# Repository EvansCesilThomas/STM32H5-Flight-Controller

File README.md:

# STM32H5 General Autopilot

A high-performance, compact autopilot utilizing the modern STM32H5 architecture.

<br>

## Features

* **Power Input:** 2S - 6S LiPo compatible
* **Dual BEC System:** 
    * `5V @ 2A` (Fixed)
    * `5V / 6V / 9V / 10V @ 2A` (Selectable)
* **Onboard Sensors:**
  * **IMU:** BMI270 or ICM-42688-P
  * **Barometer:** BMP280
  * **Compass:** QMC5883L
* **Connectivity:**
  * 6x UARTs
  * 1x I2C
  * MicroSD Card Slot
* **Signaling & Peripherals:**
  * WS2812B Addressable LED Strip Output
  * **7x Configurable GPIOs:**
    * 1x Analog Input
    * 2x Extra ESC Outputs (bringing total potential ESC outputs to 6)
    * 1x Timer Output
    * 3x Regular GPIOs
* Onboard monitoring of battery voltage and current, servo and 5V rail voltage.

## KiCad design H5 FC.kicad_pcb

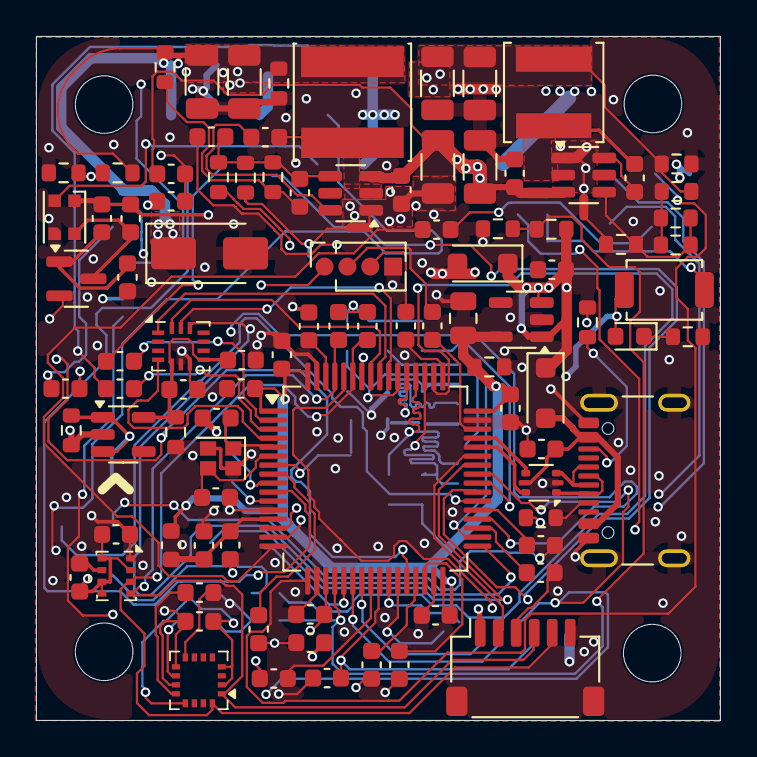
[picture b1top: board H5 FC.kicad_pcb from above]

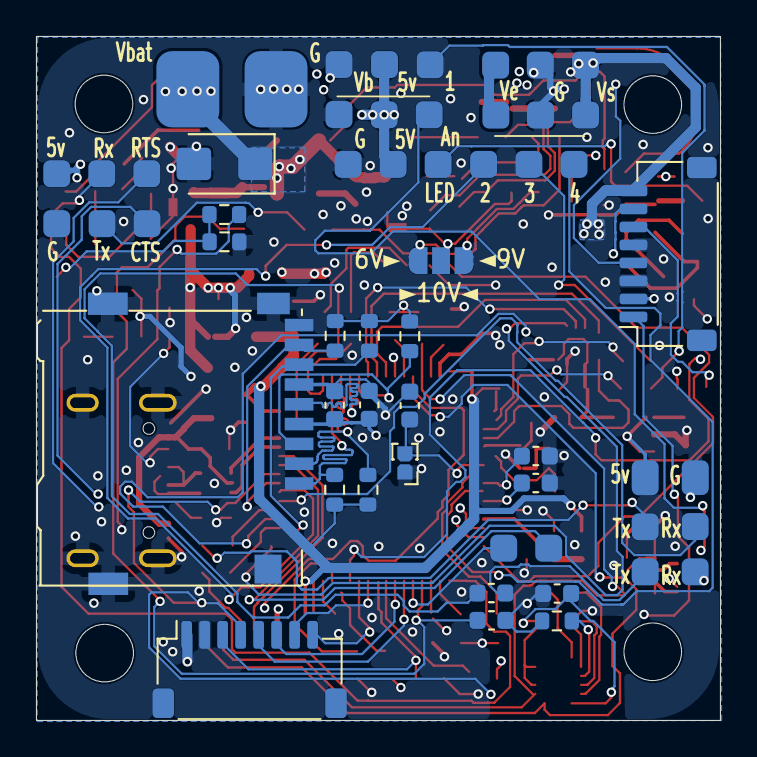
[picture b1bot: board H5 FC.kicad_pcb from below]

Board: 4 copper layers, 38.0 x 38.0 mm, 130 parts (25 on the bottom side), 99 nets.

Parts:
C1, C2: 2.2 uF; C_0603_1608Metric
C3, C9, C10, C11, C12, C13, C14, C15, C16, C17, C18, C19, C20, C21, C22, C23, C24, C26, C32, C33, C42, C43, C44, C46: 0.1uF; C_0603_1608Metric
C4, C28: 2.2uF; C_0603_1608Metric
C6, C7: 15pF; C_0603_1608Metric
C8: 4.7uF; C_0805_2012Metric
C25: 6.8uF; R_0603_1608Metric
C27: 75pF; R_0603_1608Metric
C29, C30: 2.2uF; R_0603_1608Metric
C31: 4.7uF; R_0603_1608Metric
C34, C35, C37, C38, C39, C40: 22uF; C_1206_3216Metric
C36: 75pF; C_0603_1608Metric
C41: 10uF; C_0603_1608Metric
C45: 0.22uF; C_0603_1608Metric
C47, C48: 0.1uF; R_0603_1608Metric
D1: LED; LED_0603_1608Metric
D2: SMAJ28A; D_SMA
D3: WS2812B; LED_WS2812B-2020_PLCC4_2.0x2.0mm
D4, D5: PMEG1030EH; D_SOD-123F
D7: SMAJ9.0A; D_SMA
H1, H2, H3, H4: MountingHole; MountingHole_3.2mm_M3
J1: Conn_01x04_Pin; PinSocket_1x04_P1.27mm_Vertical
J2: USB_C_Receptacle_USB2.0_16P; USB_C_Receptacle_GCT_USB4105-xx-A_16P_TopMnt_Horizontal
J3, J5: Conn_01x08; JST_SH_SM08B-SRSS-TB_1x08-1MP_P1.00mm_Horizontal
J4: Micro_SD_Card; microSD_HC_Hirose_DM3AT-SF-PEJM5
J6: Conn_01x03; JST_SH_SM04B-SRSS-TB_1x04-1MP_P1.00mm_Horizontal
J7: Conn_01x02; JST_SH_SM02B-SRSS-TB_1x02-1MP_P1.00mm_Horizontal
J8: Conn_01x05; JST_SH_BM08B-SRSS-TB_1x08-1MP_P1.00mm_Vertical
J9: Conn_01x06; JST_GH_SM05B-GHS-TB_1x05-1MP_P1.25mm_Horizontal
J13, J16, J17: Conn_01x06; JST_SH_SM06B-SRSS-TB_1x06-1MP_P1.00mm_Horizontal
J14: Conn_01x06; JST_SH_BM06B-SRSS-TB_1x06-1MP_P1.00mm_Vertical
JP2: Jumper_2_Bridged; PinHeader_1x02_P1.00mm_Vertical
JP3: SolderJumper_3_Bridged123; SolderJumper-3_P1.3mm_Bridged123_RoundedPad1.0x1.5mm_Number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
L1: 600 ohm; L_0603_1608Metric
L3: 15uH; L_Sunlord_SWPA5040S
L4: 22uH; L_Sunlord_SWPA6045S
NT1, NT2: NetTie_2; NetTie-2_SMD_Pad0.5mm
Q1: BC847; SOT-23
R1: 1.8K; R_0603_1608Metric
R2, R5, R6, R7, R8, R9, R11, R12, R24: 10K; R_0603_1608Metric
R3, R4: 5.1K; R_0603_1608Metric
R13, R18: 49.9; R_0603_1608Metric
R14: 105K; R_0603_1608Metric
R15, R20: 13.3K; R_0603_1608Metric
R17: 220; R_0603_1608Metric
R19, R23: 100K; R_0603_1608Metric
R21: 63.4K; R_0603_1608Metric
R22: 12K; C_0603_1608Metric
R25: 15K; C_0603_1608Metric
R31, R49, R50: 2.2K; C_0603_1608Metric
R32: 1K; C_0603_1608Metric
R34: 1.2K; C_0603_1608Metric
R38, R39, R40, R42, R45, R47, R48: 100; C_0603_1608Metric
R41, R46: 33; C_0603_1608Metric
R43, R44: 470; C_0603_1608Metric
R51: 4.7K; C_0603_1608Metric
R52: 10K; C_0603_1608Metric
SW1: SW_Push; SW_SPST_TS-1088-xR020
U1: STM32H562RITx; LQFP-64_10x10mm_P0.5mm
U2: BMI270; Bosch_LGA-14_3x2.5mm_P0.5mm
U3: BMP280; Bosch_LGA-8_2x2.5mm_P0.65mm_ClockwisePinNumbering
U5, U8: TPS54202DDC; SOT-23-6
U6: MIC5219-3.3YM5-MS; SOT-23-5
U7: MIC5205-3.3YM5-MS; SOT-23-5
U9: USBLC6-2P6; SOT-666
U11: QMC5883L; LGA-16_3x3mm_P0.5mm
Y2: 24 Mhz; Crystal_SMD_2016-4Pin_2.0x1.6mm

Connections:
5V_Sens: C21.1, R11.2, R12.1, U1.20 (PA4)
+3.3V: C8.1, C9.1, C10.1, C11.1, C13.1, C15.1, C18.1, C19.1, C29.1, C41.1, C42.1, C44.1, C46.1, D1.2 (A), J1.1, J4.4 (VDD), L1.1, R5.1, R6.1, R7.1, R8.1, R9.1, R49.2, R50.2, SW1.1, U1.1 (VBAT), U1.19 (VDD), U1.32 (VDD), U1.48 (VDD), U1.64 (VDD), U3.2 (CSB), U3.5 (SDO), U3.6 (VDDIO), U3.8 (VDD), U6.5 (OUT), U11.2 (VDD), U11.4 (S1), U11.13 (VDDIO)
+3.3V_IMU: C12.1, C14.1, C31.1, U2.5 (VDDIO), U2.8 (VDD), U7.5 (OUT)
+5V: C28.1, C30.1, D3.1 (VDD), D4.1 (K), D5.1 (K), J5.2, J6.3, J8.1, J13.1, J14.1, J16.1, J17.1, R11.1, R31.2, R51.2, U6.1 (IN), U6.3 (EN), U7.1 (IN), U7.3 (EN)
Analog_IN1: C22.1, J6.2, R32.1
BOOT0: R1.2, U1.60 (BOOT0)
GND: C1.2, C2.2, C3.2, C4.2, C6.2, C7.2, C8.2, C9.2, C10.2, C11.2, C12.2, C13.2, C14.2, C15.2, C16.2, C17.2, C18.2, C19.2, C20.2, C21.2, C22.2, C23.2, C25.2, C26.2, C28.2, C29.2, C30.2, C31.2, C32.2, C34.2, C35.2, C37.2, C38.2, C39.2, C40.2, C41.2, C42.2, C43.2, C44.2, C46.2, C47.2, C48.2, D2.2 (A2), D3.3 (VSS), D7.2 (A2), J1.4, J2.A1 (GND), J2.A12 (GND), J2.B1 (GND), J2.B12 (GND), J2.S1 (SHIELD), J3.2, J4.6 (VSS), J4.11 (SHIELD), J5.3, J5.5, J8.3, J8.5, J9.3, J9.4, J13.6, J14.4, J16.6, J17.6, JP2.1 (A), NT1.1, NT2.1, R2.1, R3.2, R4.2, R12.2, R17.2, R24.2, R34.2, R52.1, U1.12 (VSSA), U1.18 (VSS), U1.31 (VSS), U1.47 (VSS), U1.63 (VSS), U2.6 (GNDIO), U2.7 (GND), U3.1 (GND), U3.7 (GND), U5.1 (GND), U6.2 (GND), U7.2 (GND), U8.1 (GND), U9.2 (GND), U11.9 (GND), U11.11 (GND), Y2.2, Y2.4
GPIO1: J6.1, R44.1
GPIO2: J14.6, U1.39 (PC8)
GPIO3: J14.3, R43.1
GPIO4~_ADC: J14.5, U1.10 (PC2)
GPIO5~_ADC: J7.2, U1.21 (PA5)
GPIO6~: J7.1, U1.42 (PA9)
I2C1_SCL: J17.4, R49.1, U1.61 (PB8), U3.4 (SCK), U11.1 (SCL)
I2C1_SDA: J17.5, R50.1, U1.59 (PB7), U3.3 (SDI), U11.16 (SDA)
IBatt_Sens: C17.1, J3.3, U1.25 (PC5)
IMU_INT: U1.4 (PC15), U2.4 (INT1)
LED_OUT: Q1.2 (E), U1.28 (PB2)
LED_Strip: D3.2 (DOUT), J14.2
MOT1_PWM: J3.5, U1.22 (PA6)
MOT2_PWM: J3.6, U1.23 (PA7)
MOT3_PWM: J3.7, U1.26 (PB0)
MOT4_PWM: J3.8, U1.27 (PB1)
NRST: C26.1, JP2.2 (B), U1.7 (NRST)
unnamed: C1.1, U1.62 (VCAP)
unnamed: C2.1, U1.30 (VCAP)
unnamed: C27.1, R13.2, R14.1
unnamed: C36.1, R18.2, R19.1
unnamed: D1.1 (K), R17.1
unnamed: D3.4 (DIN), Q1.3 (C), R31.1
unnamed: J2.A5 (CC1), R4.1
unnamed: J2.B5 (CC2), R3.1
unnamed: JP3.1 (A), R25.2
unnamed: JP3.3 (B), R21.2
unnamed: JP3.2 (C), NT1.2, R20.2
unnamed: NT2.2, R15.2
unnamed: Q1.1 (B), R51.1, R52.2
unnamed: R1.1, R2.2, SW1.2
unnamed: R42.2, U1.16 (PA2)
unnamed: R47.2, U1.46 (PA13(JTMS)
unnamed: R48.2, U1.49 (PA14(JTCK)
unnamed: R46.1, U1.50 (PA15(JTDI))
unnamed: R38.1, U1.58 (PB6)
unnamed: R45.1, U1.29 (PB10)
unnamed: R40.1, U1.35 (PB14)
unnamed: R32.2, U1.8 (PC0)
unnamed: R39.2, U1.24 (PC4)
unnamed: R41.2, U1.37 (PC6)
unnamed: R43.2, U1.2 (PC13)
unnamed: R44.2, U1.3 (PC14)
unnamed: C6.1, U1.5 (PH0), Y2.1
unnamed: C7.1, U1.6 (PH1), Y2.3
unnamed: C3.1, C4.1, L1.2, U1.13 (VDDA)
unnamed: C24.1, U5.6 (BOOT)
unnamed: C27.2, R14.2, R15.1, U5.4 (FB)
unnamed: C24.2, L3.1, U5.2 (SW)
unnamed: C33.1, U8.6 (BOOT)
unnamed: C36.2, R19.2, R20.1, R21.1, R25.1, U8.4 (FB)
unnamed: C33.2, L4.1, U8.2 (SW)
unnamed: C25.1, U11.10 (C1)
unnamed: C45.1, U11.12 (SETC)
unnamed: C45.2, U11.8 (SETP)
SDMMC_CK: J4.5 (CLK), U1.53 (PC12)
SDMMC_CMD: J4.3 (CMD), R9.2, U1.54 (PD2)
SDMMC_D0: J4.7 (DAT0), R8.2, U1.34 (PB13)
SDMMC_D1: J4.8 (DAT1), R5.2, U1.40 (PC9)
SDMMC_D2: J4.1 (DAT2), R6.2, U1.51 (PC10)
SDMMC_D3: J4.2 (DAT3/CD), R7.2, U1.52 (PC11)
SPI1_CS1: U1.33 (PB12), U2.12 (CSB)
SPI1_MISO: U1.56 (PB4(NJTRST)), U2.1 (SDO)
SPI1_MOSI: U1.57 (PB5), U2.14 (SDx)
SPI1_SCK: U1.55 (PB3(JTDO), U2.13 (SCx)
SWCLK: J1.3, R48.1
SWDIO: J1.2, R47.1
UART1_RX: J17.2, U1.43 (PA10)
UART1_TX: J17.3, R40.2
UART2_CTS: J13.4, U1.14 (PA0)
UART2_RTS: J13.5, U1.15 (PA1)
UART2_RX: J13.3, U1.17 (PA3)
UART2_TX: J13.2, R42.1
UART3_RX: J5.1, R39.1
UART3_TX: J5.4, R45.2
UART5_RX: J5.7, U1.36 (PB15)
UART5_TX: J5.6, R38.2
UART6_RX: J16.3, U1.38 (PC7)
UART6_TX: J16.2, R41.1
UART7_RX: J3.4, J16.5, U1.41 (PA8)
UART7_TX: J16.4, R46.2
USB+: J2.A6 (D+), J2.B6 (D+), U9.3 (I/O2)
USB-: J2.A7 (D-), J2.B7 (D-), U9.1 (I/O1)
USB_D+: U1.45 (PA12), U9.4 (I/O2)
USB_D-: U1.44 (PA11), U9.6 (I/O1)
VBAT: C23.1, C32.1, C38.1, C39.1, D2.1 (A1), J3.1, J8.4, R22.1, U5.3 (VIN), U8.3 (VIN)
VBatt_Sens: C16.1, R22.2, R34.1, U1.9 (PC1)
V_BUCK: C37.1, C40.1, C47.1, D4.2 (A), J8.2, L3.2, R13.1
V_EXT: J9.5, J9.6
V_Servo: C34.1, C35.1, C48.1, D7.1 (A1), J5.8, J9.1, J9.2, L4.2, R18.1, R23.1
V_Servo_SENS: C20.1, R23.2, R24.1, U1.11 (PC3)
V_USB: C43.1, D5.2 (A), J2.A4 (VBUS), J2.A9 (VBUS), J2.B4 (VBUS), J2.B9 (VBUS), U9.5 (VBUS)

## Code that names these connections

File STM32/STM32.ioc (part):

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Mcu.Name=STM32H562RITx
Mcu.Package=LQFP64
Mcu.UserName=STM32H562RITx
PA0.Mode=CTS_RTS
PA0.Signal=USART2_CTS
PA1.Mode=CTS_RTS
PA1.Signal=USART2_RTS
PA10.Mode=Asynchronous
PA10.Signal=USART1_RX
PA11.Mode=Device
PA11.Signal=USB_DM
PA12.Mode=Device
PA12.Signal=USB_DP
PA13(JTMS/SWDIO).Mode=Serial_Wire
PA13(JTMS/SWDIO).Signal=DEBUG_JTMS-SWDIO
PA14(JTCK/SWCLK).Mode=Serial_Wire
PA14(JTCK/SWCLK).Signal=DEBUG_JTCK-SWCLK
PA15(JTDI).Mode=Asynchronous
PA15(JTDI).Signal=UART7_TX
PA2.Mode=Asynchronous
PA2.Signal=USART2_TX
PA3.GPIOParameters=PinAttribute
PA3.Mode=Asynchronous
PA3.PinAttribute=Free
PA3.Signal=USART2_RX
PA4.Signal=ADCx_INP18
PA5.Signal=S_TIM2_CH1
PA6.Signal=S_TIM3_CH1
PA7.Signal=S_TIM3_CH2
PA8.Mode=Asynchronous
PA8.Signal=UART7_RX
PA9.Signal=S_TIM1_CH2
PB0.Signal=S_TIM3_CH3
PB1.Signal=S_TIM3_CH4
PB10.Mode=Asynchronous
PB10.Signal=USART3_TX
PB12.Signal=GPIO_Output
PB13.Mode=sdio_4_bits_Wide_bus
PB13.Signal=SDMMC1_D0
PB14.GPIOParameters=PinAttribute
PB14.Mode=Asynchronous
PB14.PinAttribute=Free
PB14.Signal=USART1_TX
PB15.GPIOParameters=PinAttribute
PB15.Mode=Asynchronous
PB15.PinAttribute=Free
PB15.Signal=UART5_RX
PB2.Mode=PWM Generation4 CH4N
PB2.Signal=TIM8_CH4N
PB3(JTDO/TRACESWO).Mode=Full_Duplex_Master
PB3(JTDO/TRACESWO).Signal=SPI1_SCK
PB4(NJTRST).Mode=Full_Duplex_Master
PB4(NJTRST).Signal=SPI1_MISO
PB5.Mode=Full_Duplex_Master
PB5.Signal=SPI1_MOSI
PB6.Mode=Asynchronous
PB6.Signal=UART5_TX
PB7.Mode=I2C
PB7.Signal=I2C1_SDA
PB8.Mode=I2C
PB8.Signal=I2C1_SCL
PC0.Signal=ADCx_INP10
PC1.Signal=ADCx_INP11
PC10.GPIOParameters=PinAttribute
PC10.Mode=sdio_4_bits_Wide_bus
PC10.PinAttribute=Free
PC10.Signal=SDMMC1_D2
PC11.Mode=sdio_4_bits_Wide_bus
PC11.Signal=SDMMC1_D3
PC12.Mode=sdio_4_bits_Wide_bus
PC12.Signal=SDMMC1_CK
PC13.GPIOParameters=PinAttribute
PC13.PinAttribute=Free
PC13.Signal=GPIO_Output
PC14-OSC32_IN(OSC32_IN).GPIOParameters=PinAttribute
PC14-OSC32_IN(OSC32_IN).PinAttribute=Free
PC14-OSC32_IN(OSC32_IN).Signal=GPIO_Output
PC15-OSC32_OUT(OSC32_OUT).Signal=GPIO_Output
PC2.Signal=S_TIM4_CH4
PC3.Signal=ADCx_INP13
PC4.Mode=Asynchronous
PC4.Signal=USART3_RX
PC5.Signal=ADCx_INP8
PC6.Mode=Asynchronous
PC6.Signal=USART6_TX
PC7.Mode=Asynchronous
PC7.Signal=USART6_RX
PC8.Signal=S_TIM8_CH3
PC9.Mode=sdio_4_bits_Wide_bus
PC9.Signal=SDMMC1_D1
PD2.Mode=sdio_4_bits_Wide_bus
PD2.Signal=SDMMC1_CMD
PH0-OSC_IN(PH0).Mode=HSE-External-Oscillator
PH0-OSC_IN(PH0).Signal=RCC_OSC_IN
PH1-OSC_OUT(PH1).Mode=HSE-External-Oscillator
PH1-OSC_OUT(PH1).Signal=RCC_OSC_OUT
RCC.HSE_VALUE=24000000
RCC.SYSCLKFreq_VALUE=250000000
RCC.SYSCLKSource=RCC_SYSCLKSOURCE_PLLCLK
board=custom

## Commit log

2026-06-11 Add README
    Add README
    Add README
    Add README
    Add README
2026-06-11 Add V1.1
    Add V1.1
    Add V1.1
2026-06-11 Update README
    Update README
2026-06-11 v1.1.1 layout version
    v1.1.1 layout version
2026-06-13 v1.2
    v1.2
2026-06-20 Improve board
